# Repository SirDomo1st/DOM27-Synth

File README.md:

# D.O.M-27 Synth

My project is a fully DIY & anaglouge modular synth based on the eurorack system. It features 4 fundemental components of synthesis - a VCO, LFO, VCF & VCA. Because it is a modular synth & based on eurorack, this means that I can create more modules when I please to expand the functionality of my synth. There is no bottom case on the pannels as they are intended to me rack mounted on a system called eurorack. [Something like this](https://synthracks.com/shop/12u-studio-case?srsltid=AfmBOooeTvIxWJoqXPR5WksLaoWv1k82hauFViBRm4C1jTSQUN6ccUx9)

I made this my project is due to my passion for synth music and a want to learn to electronics. This was perfect as I could learn some basics of anaglouge electronics while also creating a useable, musical instrument. It was also perfect because modular synthesis is 
typically a very expensive hobby to get into.

### Total time spent on project: ~23 hours

## All 4 modules together 

## VCA pcb

## LFO pcb

## VCO pcb

## VCF pcb

## Project Schematics

Synth pannel CAD source files: https://www.mediafire.com/folder/19pjphztzjj5q/Synth+Pannel

A psu is included in my BOM because a eurorack system has specific power requiremnets. The psu sends +12v, -12v, 5v & GND to each individual module. It can also carry CV information. The psu also has a daisy chain ribbon as each module is powered individually. This is why they are fairly expensive, but also why one is required.

# D.O.M 27 Synth Bill of Materials
# Synthesizer Bill of Materials

| Value | Qty | Footprint | Source | Price | Where from |
|-------|-----|-----------|--------|-------|------------|
| 1.5k | 1 | Resistor_THT:R_Axial_DIN0207_L6.3mm_D2.5mm_P7.62mm_Horizontal | DS-20 VCF | 0.12 | Tayda |
| 100k | 44 | Resistor_THT:R_Axial_DIN0207_L6.3mm_D2.5mm_P7.62mm_Horizontal | DOMSynth, DS-20 VCF, Dom LFO, Dom VCA | 1.25 | Tayda |
| 100n | 4 | Capacitor_THT:C_Disc_D5.0mm_W2.5mm_P5.00mm | DS-20 VCF | 0.4 | Tayda |
| 10k | 27 | Resistor_THT:R_Axial_DIN0207_L6.3mm_D2.5mm_P7.62mm_Horizontal | DOMSynth, DS-20 VCF, Dom LFO, Dom VCA | 2.7 | Tayda |
| 10u | 4 | Capacitor_THT:C_Disc_D3.0mm_W1.6mm_P2.50mm | DS-20 VCF, Dom VCA | 0.15 | Tayda |
| 14k | 1 | Resistor_THT:R_Axial_DIN0207_L6.3mm_D2.5mm_P7.62mm_Horizontal | DOMSynth | ---- | |
| 150k | 2 | Resistor_THT:R_Axial_DIN0207_L6.3mm_D2.5mm_P7.62mm_Horizontal | Dom LFO | 0.25 | Tayda |
| 15k | 13 | Resistor_THT:R_Axial_DIN0207_L6.3mm_D2.5mm_P7.62mm_Horizontal | Dom VCA | 0.3 | Tayda |
| 1M | 3 | Resistor_THT:R_Axial_DIN0207_L6.3mm_D2.5mm_P7.62mm_Horizontal | DOMSynth | 0.15 | Tayda |
| 1N4148 | 5 | Diode_THT:D_DO-35_SOD27_P7.62mm_Horizontal | DOMSynth, Dom LFO | 0.05 | Tayda |
| 1k | 23 | Resistor_THT:R_Axial_DIN0207_L6.3mm_D2.5mm_P7.62mm_Horizontal | DOMSynth, DS-20 VCF, Dom LFO, Dom VCA | 0.45 | Tayda |
| 1k5 | 1 | Resistor_THT:R_Axial_DIN0207_L6.3mm_D2.5mm_P7.62mm_Horizontal | DOMSynth | 0.15 | Tayda |
| 1n | 2 | Capacitor_THT:C_Disc_D5.0mm_W2.5mm_P5.00mm | DS-20 VCF | 0.9 | Tayda |
| 1µF | 1 | Capacitor_THT:C_Disc_D5.0mm_W2.5mm_P5.00mm | DOMSynth | 0.12 | Tayda |
| 2.2k | 2 | Resistor_THT:R_Axial_DIN0207_L6.3mm_D2.5mm_P7.62mm_Horizontal | Dom LFO | 0.15 | Tayda |
| 2.2nF | 1 | Capacitor_THT:C_Disc_D5.0mm_W2.5mm_P5.00mm | DOMSynth | 0.06 | Tayda |
| 200k | 3 | Resistor_THT:R_Axial_DIN0207_L6.3mm_D2.5mm_P7.62mm_Horizontal | Dom VCA | 0.12 | Tayda |
| 220 | 4 | Resistor_THT:R_Axial_DIN0207_L6.3mm_D2.5mm_P7.62mm_Horizontal | DS-20 VCF | 0.8 | Tayda |
| 220k | 1 | Resistor_THT:R_Axial_DIN0207_L6.3mm_D2.5mm_P7.62mm_Horizontal | DS-20 VCF | 0.15 | Tayda |
| 250k | 1 | Potentiometer_THT:Potentiometer_Alpha_RD901F-40-00D_Single_Vertical | DOMSynth | 1.29 | Tayda |
| 33k | 4 | Resistor_THT:R_Axial_DIN0207_L6.3mm_D2.5mm_P7.62mm_Horizontal | DOMSynth, Dom VCA | 0.15 | Tayda |
| 4.7k | 5 | Resistor_THT:R_Axial_DIN0207_L6.3mm_D2.5mm_P7.62mm_Horizontal | DS-20 VCF, Dom LFO | 0.15 | Tayda |
| 4.7n | 1 | Capacitor_THT:C_Disc_D5.0mm_W2.5mm_P5.00mm | DS-20 VCF | 0.07 | Tayda |
| 470k | 1 | Resistor_THT:R_Axial_DIN0207_L6.3mm_D2.5mm_P7.62mm_Horizontal | DS-20 VCF | 0.15 | Tayda |
| 470n | 1 | Capacitor_THT:C_Disc_D5.0mm_W2.5mm_P5.00mm | DS-20 VCF | 0.08 | Tayda |
| 47k | 1 | Resistor_THT:R_Axial_DIN0207_L6.3mm_D2.5mm_P7.62mm_Horizontal | DS-20 VCF | 0.15 | Tayda |
| 47n | 2 | Capacitor_THT:C_Disc_D5.0mm_W2.5mm_P5.00mm | Dom LFO | 0.13 | Tayda |
| 500k | 2 | Potentiometer_THT:Potentiometer_Alpha_RD901F-40-00D_Single_Vertical | Dom LFO | 1.34 | Tayda |
| 5k | 3 | Potentiometer_THT:Potentiometer_Bourns_3296P_Horizontal | Dom VCA | 0.18 | Tayda |
| 68k | 2 | Resistor_THT:R_Axial_DIN0207_L6.3mm_D2.5mm_P7.62mm_Horizontal | DOMSynth | 0.15 | Tayda |
| 74HC14 | 1 | Package_DIP:DIP-14_W7.62mm | DOMSynth | 0.66 | Tayda |
| Audio Jack | 23 | Connector_Audio:Jack_3.5mm_QingPu_WQP-PJ398SM_Vertical_CircularHoles | DOMSynth, DS-20 VCF, Dom LFO, Dom VCA | 8.97 | Tayda |
| BC548 | 10 | Package_TO_SOT_THT:TO-92_Inline | DOMSynth, Dom VCA | 0.4 | Tayda |
| BC557 | 2 | Package_TO_SOT_THT:TO-92_Inline | DS-20 VCF | 0.06 | Tayda |
| BC558 | 1 | Package_TO_SOT_THT:TO-92_Inline | DOMSynth | 0.04 | Tayda |
| 10u Polarised | 2 | Capacitor_THT:CP_Radial_D5.0mm_P2.50mm | Dom VCA | 0.06 | Tayda |
| Conn_02x08_Odd_Even | 2 | Connector_IDC:IDC-Header_2x08_P2.54mm_Vertical | DS-20 VCF, Dom VCA | --- | |
| Conn_02x08_Top_Bottom | 2 | Connector_IDC:IDC-Header_2x08_P2.54mm_Vertical | DOMSynth, Dom LFO | --- | |
| LED | 2 | LED_THT:LED_D5.0mm | DS-20 VCF | 0.048 | Tayda |
| LM13700 | 2 | Package_TO_SOT_SMD:SOT-23-5 | DS-20 VCF | 4.7 | Tayda |
| TL072 | 10 | Package_DIP:DIP-8_W7.62mm | DS-20 VCF, Dom VCA | 14.9 | Tayda |
| TL074 | 8 | Package_DIP:DIP-14_W7.62mm | DOMSynth, Dom LFO | 4.72 | Tayda |
| 100k | 13 | Pot | | 8.71 | Tayda |
| 10k | 1 | Pot | | 0.67 | Tayda |
| 1M | 1 | Pot | | 0.67 | Tayda |
| 1k | 2 | MusicThingModular:BOURNS_3362P_TRIMMER | | 0.12 | Tayda |
| 10k | 3 | Potentiometer_THT:Potentiometer_Bourns_3296P_Horizontal | | 0.18 | Tayda |
| | | | | | Tayda |
| Power Male | 4 | | | 1.2 | |
| Power Female | 4 | | | 0.52 | |
| Tayda Shipping | 1 | | | 9.25 | Tayda |
| | | | | | |
| PSU | 1 | Behringer System 55 CP1A Power Supply Module | | 62.56 | Gear4Music |
| G4M Shipping | | | | 2.71 | |
| | | | | | |
| PCB 110x60 | 2 | | | 13 | JLB PCB |
| PCB 110x40 | 2 | | | 11.4 | JLB PCB |
| JLB Shipping | 1 | | | 3.12 | |
| | | | | | |
| **Total Price** | | | | **$160.77** |

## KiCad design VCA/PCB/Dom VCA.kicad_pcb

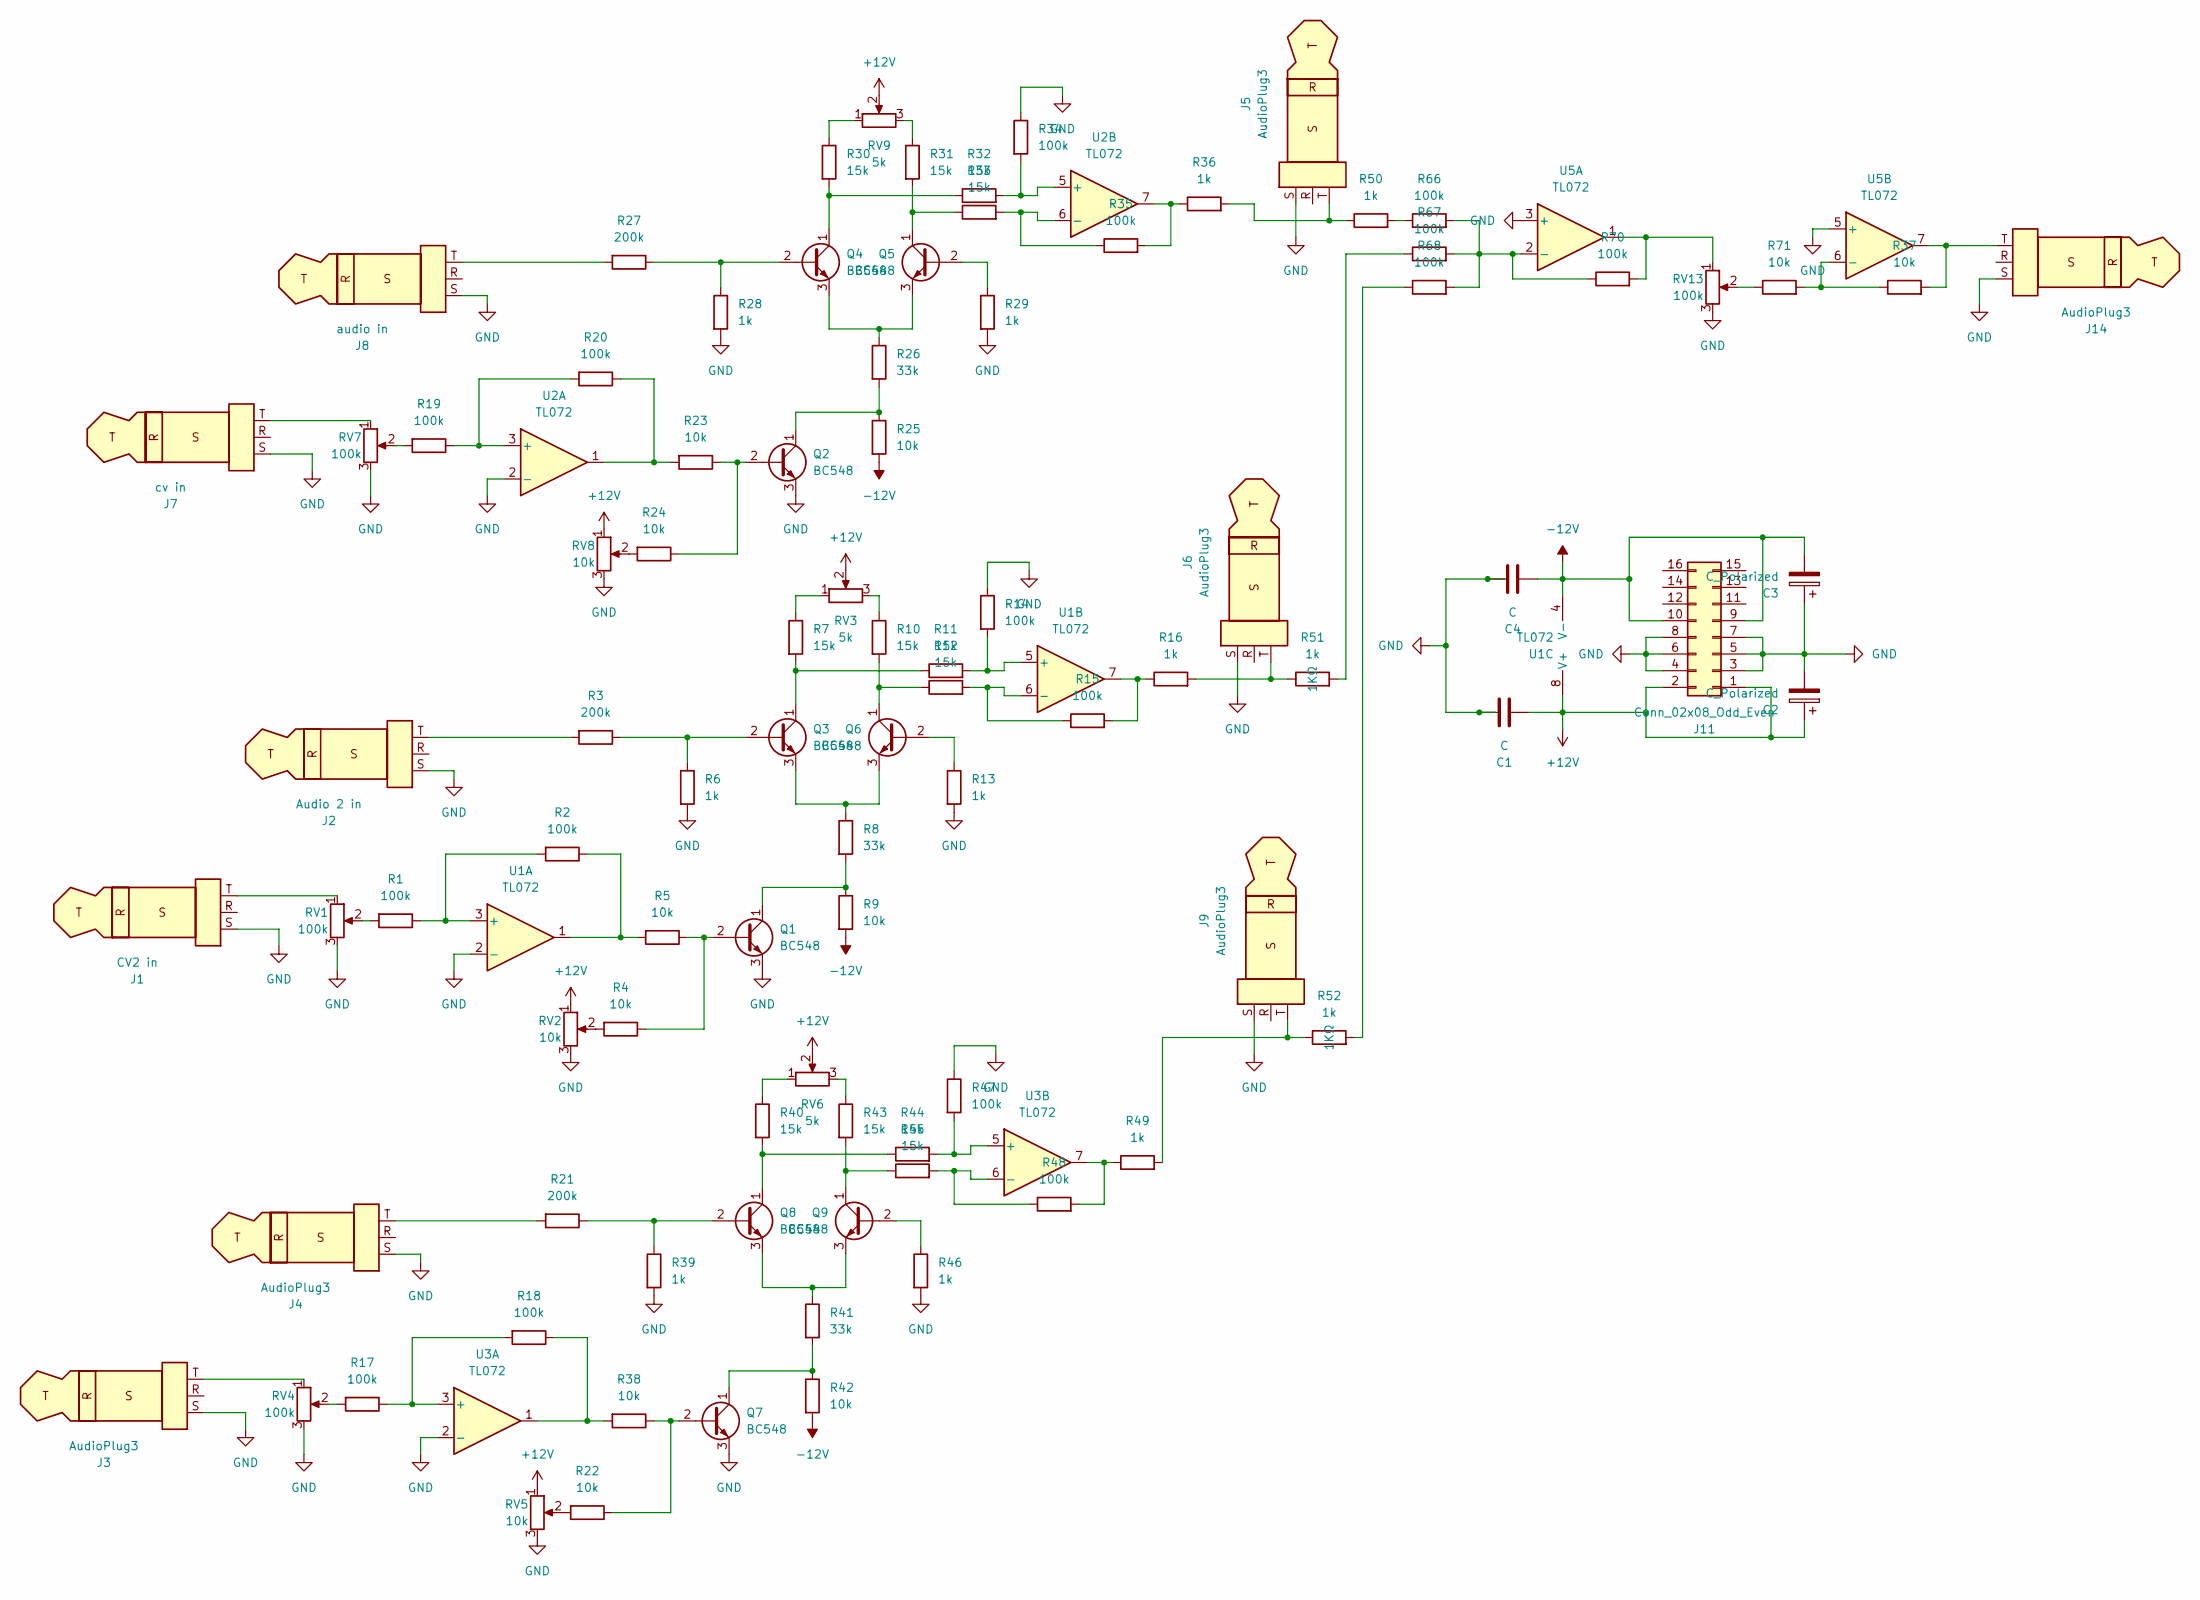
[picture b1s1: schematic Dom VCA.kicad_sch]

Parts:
C1, C4: C; C_Disc_D3.0mm_W1.6mm_P2.50mm
C2, C3: C_Polarized; CP_Radial_D5.0mm_P2.50mm
J1: CV2 in; Jack_3.5mm_QingPu_WQP-PJ398SM_Vertical_CircularHoles
J2: Audio 2 in; Jack_3.5mm_QingPu_WQP-PJ398SM_Vertical_CircularHoles
J3, J4, J5, J6, J9, J14: AudioPlug3; Jack_3.5mm_QingPu_WQP-PJ398SM_Vertical_CircularHoles
J7: cv in; Jack_3.5mm_QingPu_WQP-PJ398SM_Vertical_CircularHoles
J8: audio in; Jack_3.5mm_QingPu_WQP-PJ398SM_Vertical_CircularHoles
J11: Conn_02x08_Odd_Even; IDC-Header_2x08_P2.54mm_Vertical
Q1, Q2, Q3, Q4, Q5, Q6, Q7, Q8, Q9: BC548; TO-92_Inline
R1, R2, R14, R15, R17, R18, R19, R20, R34, R35, R47, R48, R66, R67, R68, R70: 100k; R_Axial_DIN0207_L6.3mm_D2.5mm_P7.62mm_Horizontal
R3, R21, R27: 200k; R_Axial_DIN0207_L6.3mm_D2.5mm_P7.62mm_Horizontal
R4, R5, R9, R22, R23, R24, R25, R37, R38, R42, R71: 10k; R_Axial_DIN0207_L6.3mm_D2.5mm_P7.62mm_Horizontal
R6, R13, R16, R28, R29, R36, R39, R46, R49, R50, R51, R52: 1k; R_Axial_DIN0207_L6.3mm_D2.5mm_P7.62mm_Horizontal
R7, R10, R11, R12, R30, R31, R32, R33, R40, R43, R44, R45: 15k; R_Axial_DIN0207_L6.3mm_D2.5mm_P7.62mm_Horizontal
R8, R26, R41: 33k; R_Axial_DIN0207_L6.3mm_D2.5mm_P7.62mm_Horizontal
RV1, RV4, RV7, RV13: 100k; Potentiometer_Alpha_RD901F-40-00D_Single_Vertical
RV2, RV5, RV8: 10k; Potentiometer_Bourns_3296P_Horizontal
RV3, RV6, RV9: 5k; Potentiometer_Bourns_3296P_Horizontal
U1, U2, U3, U5: TL072; DIP-8_W7.62mm

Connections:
+12V: C1.1, C2.1, J11.1, J11.2, RV2.1, RV3.2, RV5.1, RV6.2, RV8.1, RV9.2, U1.8 (V+)
-12V: C3.2, C4.1, J11.9, J11.10, R9.2, R25.2, R42.2, U1.4 (V-)
GND: C1.2, C2.2, C3.1, C4.2, J1.S, J2.S, J3.S, J4.S, J5.S, J6.S, J7.S, J8.S, J9.S, J11.3, J11.4, J11.5, J11.6, J11.7, J11.8, J14.S, Q1.3 (E), Q2.3 (E), Q7.3 (E), R6.2, R13.2, R14.1, R28.2, R29.2, R34.1, R39.2, R46.2, R47.1, RV1.3, RV2.3, RV4.3, RV5.3, RV7.3, RV8.3, RV13.3, U1.2 (-), U2.2 (-), U3.2 (-), U5.3 (+), U5.5 (+)
unnamed: J1.T, RV1.1
unnamed: J2.T, R3.2
unnamed: J3.T, RV4.1
unnamed: J4.T, R21.2
unnamed: J5.T, R36.2, R50.1
unnamed: J6.T, R16.2, R51.1
unnamed: J7.T, RV7.1
unnamed: J8.T, R27.2
unnamed: J9.T, R49.2, R52.1
unnamed: J14.T, R37.2, U5.7
unnamed: Q1.2 (B), R4.1, R5.1
unnamed: Q1.1 (C), R8.2, R9.1
unnamed: Q2.2 (B), R23.1, R24.1
unnamed: Q2.1 (C), R25.1, R26.2
unnamed: Q3.2 (B), R3.1, R6.1
unnamed: Q3.1 (C), R7.2, R11.1
unnamed: Q3.3 (E), Q6.3 (E), R8.1
unnamed: Q4.2 (B), R27.1, R28.1
unnamed: Q4.1 (C), R30.2, R32.1
unnamed: Q4.3 (E), Q5.3 (E), R26.1
unnamed: Q5.2 (B), R29.1
unnamed: Q5.1 (C), R31.2, R33.1
unnamed: Q6.2 (B), R13.1
unnamed: Q6.1 (C), R10.2, R12.1
unnamed: Q7.2 (B), R22.1, R38.1
unnamed: Q7.1 (C), R41.2, R42.1
unnamed: Q8.2 (B), R21.1, R39.1
unnamed: Q8.1 (C), R40.2, R44.1
unnamed: Q8.3 (E), Q9.3 (E), R41.1
unnamed: Q9.2 (B), R46.1
unnamed: Q9.1 (C), R43.2, R45.1
unnamed: R1.2, RV1.2
unnamed: R2.1, R5.2, U1.1
unnamed: R4.2, RV2.2
unnamed: R7.1, RV3.1
unnamed: R10.1, RV3.3
unnamed: R15.2, R16.1, U1.7
unnamed: R17.2, RV4.2
unnamed: R18.1, R38.2, U3.1
unnamed: R19.2, RV7.2
unnamed: R20.1, R23.2, U2.1
unnamed: R22.2, RV5.2
unnamed: R24.2, RV8.2
unnamed: R30.1, RV9.1
unnamed: R31.1, RV9.3
unnamed: R35.2, R36.1, U2.7
unnamed: R40.1, RV6.1
unnamed: R43.1, RV6.3
unnamed: R48.2, R49.1, U3.7
unnamed: R50.2, R66.1
unnamed: R51.2, R67.1
unnamed: R52.2, R68.1
unnamed: R70.2, RV13.1, U5.1
unnamed: R71.1, RV13.2
unnamed: R1.1, R2.2, U1.3 (+)
unnamed: R11.2, R14.2, U1.5 (+)
unnamed: R12.2, R15.1, U1.6 (-)
unnamed: R19.1, R20.2, U2.3 (+)
unnamed: R32.2, R34.2, U2.5 (+)
unnamed: R33.2, R35.1, U2.6 (-)
unnamed: R17.1, R18.2, U3.3 (+)
unnamed: R44.2, R47.2, U3.5 (+)
unnamed: R45.2, R48.1, U3.6 (-)
unnamed: R66.2, R67.2, R68.2, R70.1, U5.2 (-)
unnamed: R37.1, R71.2, U5.6 (-)

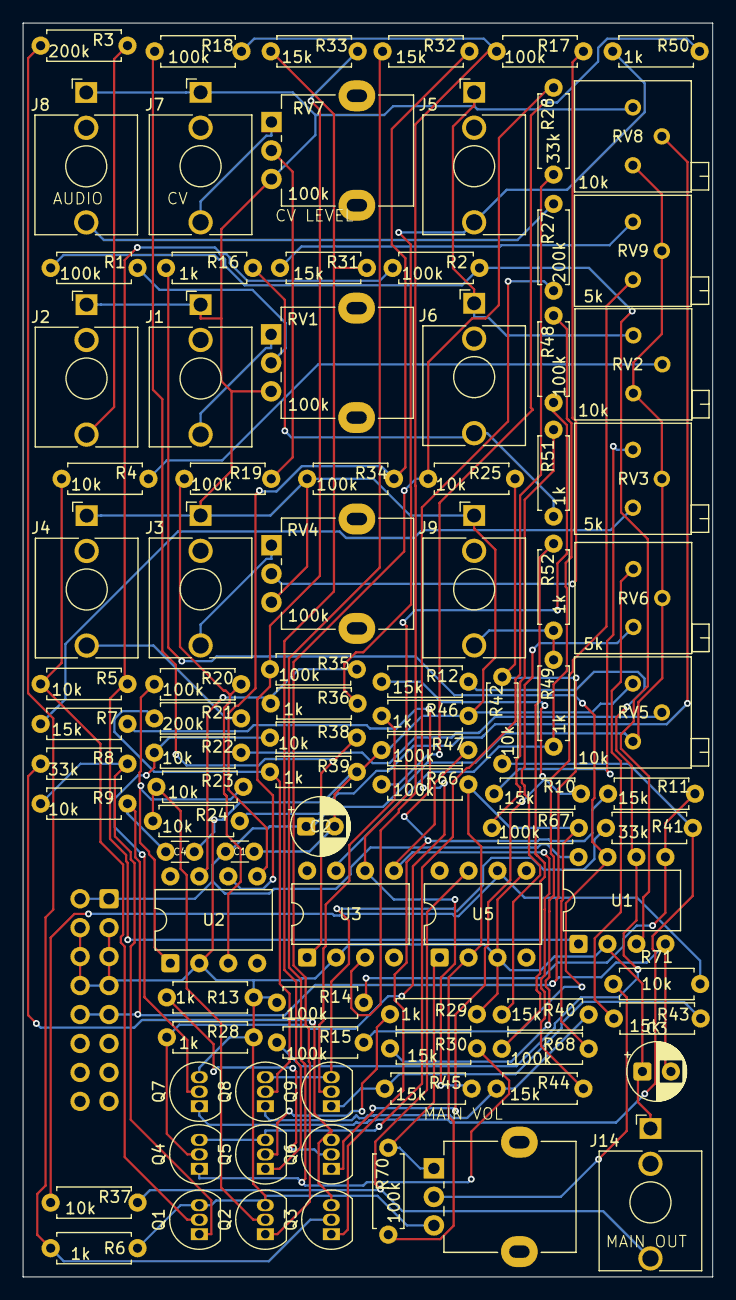
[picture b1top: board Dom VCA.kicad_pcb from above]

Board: 2 copper layers, 60.5 x 110.0 mm, 95 parts (1 on the bottom side), 68 nets.

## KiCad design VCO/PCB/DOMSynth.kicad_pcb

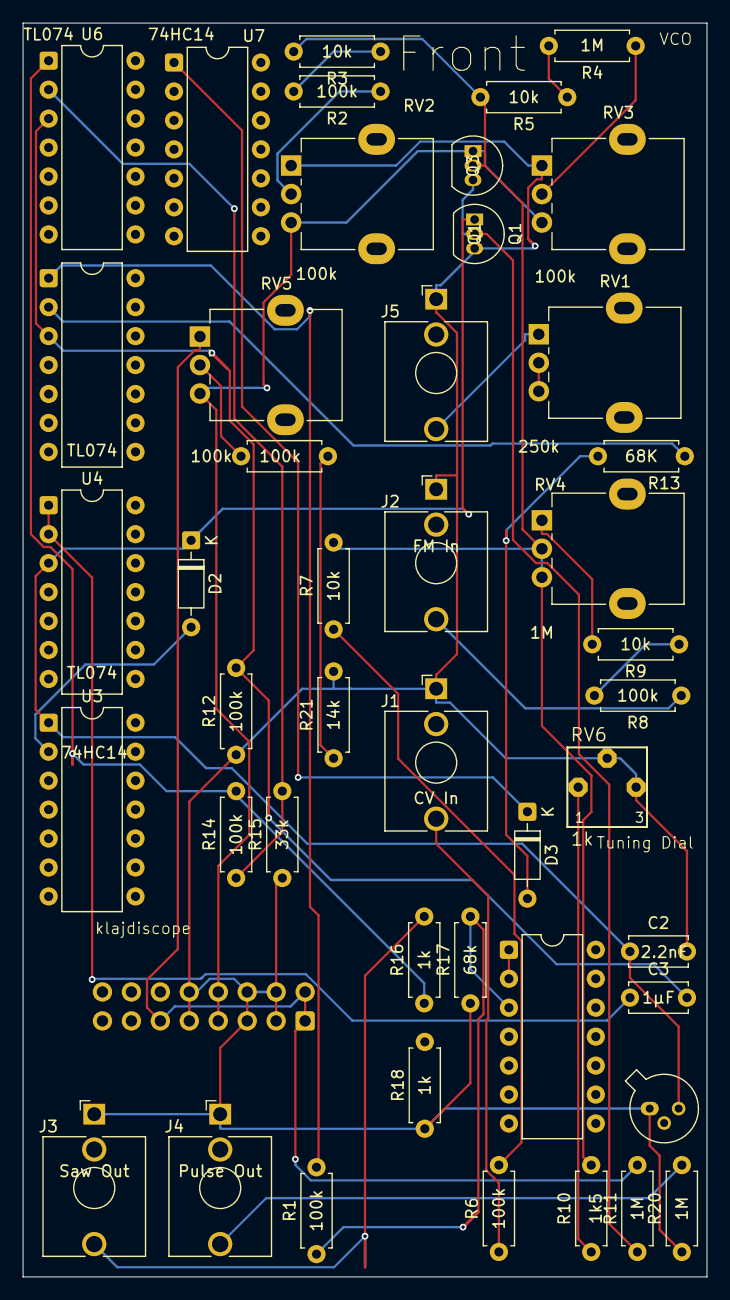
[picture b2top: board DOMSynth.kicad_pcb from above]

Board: 2 copper layers, 60.0 x 110.0 mm, 46 parts (1 on the bottom side), 33 nets.

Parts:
C2: 2.2nF; C_Disc_D5.0mm_W2.5mm_P5.00mm
C3: 1µF; C_Disc_D5.0mm_W2.5mm_P5.00mm
D2, D3: 1N4148; D_DO-35_SOD27_P7.62mm_Horizontal
J1: CV In; Jack_3.5mm_QingPu_WQP-PJ398SM_Vertical_CircularHoles
J2: FM In; Jack_3.5mm_QingPu_WQP-PJ398SM_Vertical_CircularHoles
J3: Saw Out; Jack_3.5mm_QingPu_WQP-PJ398SM_Vertical_CircularHoles
J4: Pulse Out; Jack_3.5mm_QingPu_WQP-PJ398SM_Vertical_CircularHoles
J5: PMW In; Jack_3.5mm_QingPu_WQP-PJ398SM_Vertical_CircularHoles
J6: Conn_02x08_Top_Bottom; IDC-Header_2x08_P2.54mm_Vertical
Q1: BC548; TO-92_Inline
Q3: BC558; TO-92_Inline
Q5: BC107; TO-18-3
R1, R2, R6, R8, R12, R14, R22: 100k; R_Axial_DIN0207_L6.3mm_D2.5mm_P7.62mm_Horizontal
R3, R5, R7, R9: 10k; R_Axial_DIN0207_L6.3mm_D2.5mm_P7.62mm_Horizontal
R4, R11, R20: 1M; R_Axial_DIN0207_L6.3mm_D2.5mm_P7.62mm_Horizontal
R10: 1k5; R_Axial_DIN0207_L6.3mm_D2.5mm_P7.62mm_Horizontal
R13: 68K; R_Axial_DIN0207_L6.3mm_D2.5mm_P7.62mm_Horizontal
R15: 33k; R_Axial_DIN0207_L6.3mm_D2.5mm_P7.62mm_Horizontal
R16, R18: 1k; R_Axial_DIN0207_L6.3mm_D2.5mm_P7.62mm_Horizontal
R17: 68k; R_Axial_DIN0207_L6.3mm_D2.5mm_P7.62mm_Horizontal
R21: 14k; R_Axial_DIN0207_L6.3mm_D2.5mm_P7.62mm_Horizontal
RV1: 250k; Potentiometer_Alpha_RD901F-40-00D_Single_Vertical
RV2, RV3, RV5: 100k; Potentiometer_Alpha_RD901F-40-00D_Single_Vertical
RV4: 1M; Potentiometer_Alpha_RD901F-40-00D_Single_Vertical
RV6: 1k; BOURNS_3362P_TRIMMER
U1, U4, U5, U6: TL074; DIP-14_W7.62mm
U3, U7: 74HC14; DIP-14_W7.62mm

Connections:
+12V: J6.1, J6.2, J6.11, R11.2, RV5.1
-12V: J6.7, J6.8, Q3.1 (C), RV2.3, RV3.3, RV5.3
GND: C2.2, J1.S, J2.S, J3.S, J4.S, J5.S, J6.3, J6.4, J6.5, J6.6, J6.9, J6.10, Q1.3 (E), Q5.1 (E), R12.1, R15.1, R17.1, R18.1, R20.1, R21.2, RV2.1, RV3.1, RV6.2, RV6.3
unnamed: D2.2 (A), U3.2
unnamed: C2.1, D2.1 (K), Q1.1 (C), Q5.3 (C), U3.1, U4.3 (+)
unnamed: D3.2 (A), R13.2
unnamed: D3.1 (K), U7.1
unnamed: J1.T, R6.1
unnamed: J2.T, R8.1
unnamed: J3.T, R16.2
unnamed: J4.T, R20.2
unnamed: J5.T, RV1.1
unnamed: Q1.2 (B), Q3.3 (E), R11.1
unnamed: Q3.2 (B), R3.2, R5.2, R7.2, R10.2, RV4.2, RV4.3
unnamed: R1.2, U5.1
unnamed: R2.1, RV2.2
unnamed: R2.2, R3.1
unnamed: R4.1, RV3.2
unnamed: R4.2, R5.1
unnamed: R6.2, R7.1
unnamed: R8.2, R9.1
unnamed: R9.2, RV4.1
unnamed: R10.1, RV6.1
unnamed: RV1.2, RV1.3
unnamed: R14.2, R16.1, U6.1
unnamed: R21.1, R22.2
unnamed: R22.1, RV5.2
unnamed: R1.1, R17.2, U1.3 (+)
unnamed: U1.1, U1.2 (-)
unnamed: C3.1, U4.1, U4.2 (-)
unnamed: C3.2, R12.2, U5.3 (+), U6.3 (+)
unnamed: R13.1, U5.2 (-)
unnamed: R14.1, R15.2, U6.2 (-)

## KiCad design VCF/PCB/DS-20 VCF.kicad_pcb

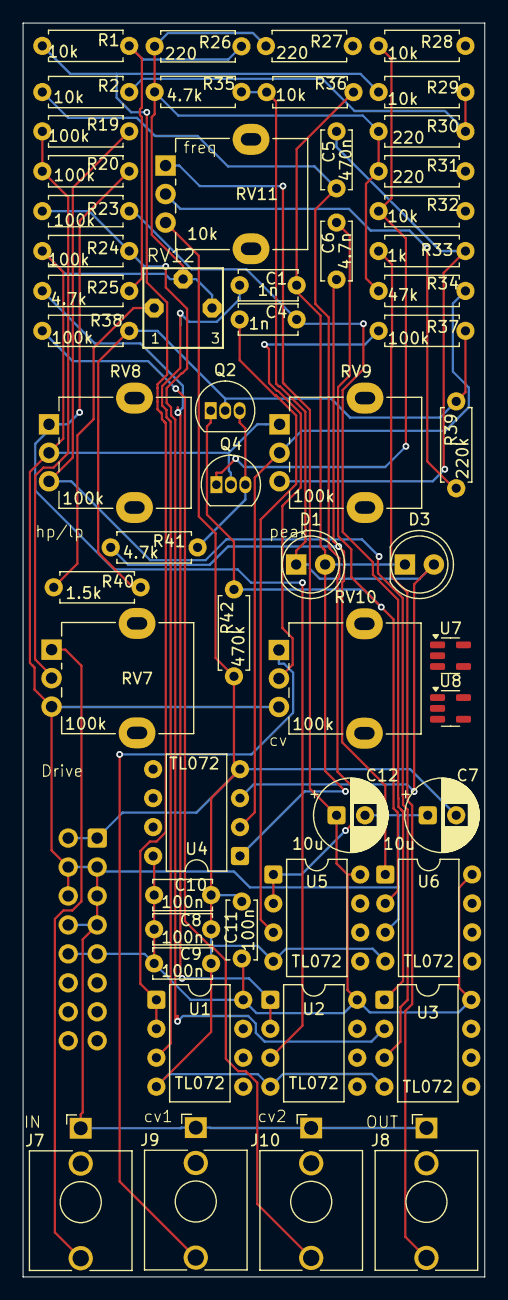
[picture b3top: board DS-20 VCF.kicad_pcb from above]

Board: 2 copper layers, 40.5 x 110.0 mm, 57 parts (1 on the bottom side), 31 nets.

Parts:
C1, C4: 1n; C_Disc_D5.0mm_W2.5mm_P5.00mm
C5: 470n; C_Disc_D5.0mm_W2.5mm_P5.00mm
C6: 4.7n; C_Disc_D5.0mm_W2.5mm_P5.00mm
C7, C12: 10u; CP_Radial_D6.3mm_P2.50mm
C8, C9, C10, C11: 100n; C_Disc_D5.0mm_W2.5mm_P5.00mm
D1, D3: LED; LED_D5.0mm
J7, J8, J9, J10: AudioPlug3; Jack_3.5mm_QingPu_WQP-PJ398SM_Vertical_CircularHoles
J12: Conn_02x08_Odd_Even; IDC-Header_2x08_P2.54mm_Vertical
Q2, Q4: BC557; TO-92_Inline
R1, R2, R28, R29, R32, R36: 10k; R_Axial_DIN0207_L6.3mm_D2.5mm_P7.62mm_Horizontal
R19, R20, R23, R24, R37, R38: 100k; R_Axial_DIN0207_L6.3mm_D2.5mm_P7.62mm_Horizontal
R25, R35, R41: 4.7k; R_Axial_DIN0207_L6.3mm_D2.5mm_P7.62mm_Horizontal
R26, R27, R30, R31: 220; R_Axial_DIN0207_L6.3mm_D2.5mm_P7.62mm_Horizontal
R33: 1k; R_Axial_DIN0207_L6.3mm_D2.5mm_P7.62mm_Horizontal
R34: 47k; R_Axial_DIN0207_L6.3mm_D2.5mm_P7.62mm_Horizontal
R39: 220k; R_Axial_DIN0207_L6.3mm_D2.5mm_P7.62mm_Horizontal
R40: 1.5k; R_Axial_DIN0207_L6.3mm_D2.5mm_P7.62mm_Horizontal
R42: 470k; R_Axial_DIN0207_L6.3mm_D2.5mm_P7.62mm_Horizontal
RV7, RV8, RV9, RV10: 100k; Potentiometer_Alpha_RD901F-40-00D_Single_Vertical
RV11: 10k; Potentiometer_Alpha_RD901F-40-00D_Single_Vertical
RV12: 1k; BOURNS_3362P_TRIMMER
U1, U2, U3, U4, U5, U6: TL072; DIP-8_W7.62mm
U7, U8: LM13700; SOT-23-5

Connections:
+12V: C8.1, C9.1, C10.1, C11.1, C12.1, J12.9, J12.10, RV11.1, U1.8 (V+), U2.8 (V+), U3.8 (V+), U4.8 (V+), U5.8 (V+), U6.8 (V+)
-12V: C7.2, C8.2, C9.2, C10.2, C11.2, J12.1, J12.2, R42.1, RV11.3, U1.4 (V-), U2.4 (V-), U3.4 (V-), U4.4 (V-), U5.4 (V-), U6.4 (V-)
GND: C7.1, C12.2, J7.S, J8.S, J9.S, J10.S, J12.3, J12.4, J12.5, J12.6, J12.7, J12.8, Q4.2 (B), R24.1, R26.1, R27.1, R30.1, R31.1, R34.1, R35.1, RV7.3, RV8.2, RV9.1, RV10.3, RV12.2, RV12.3, U6.3 (+)
unnamed: C4.2, R23.2, U3.1
unnamed: C5.2, R33.2, RV9.3
unnamed: C6.1, R41.1, U6.1
unnamed: C1.2, D1.2 (A), D3.1 (K), R36.2, U4.1
unnamed: D1.1 (K), D3.2 (A), R35.2, R36.1, U4.3 (+)
unnamed: J7.T, RV7.1
unnamed: J8.T, R33.1
unnamed: J9.T, RV10.1
unnamed: J10.T, R38.1
unnamed: Q2.2 (B), R37.2, R38.2, R39.2, R40.2
unnamed: C6.2, Q2.1 (C), R42.2, U6.2 (-)
unnamed: Q2.3 (E), Q4.3 (E), R41.2
unnamed: Q4.1 (C), R28.1, R32.1
unnamed: R19.1, R20.1, RV7.2
unnamed: R37.1, RV10.2
unnamed: R39.1, RV11.2
unnamed: R40.1, RV12.1
unnamed: C1.1, U1.3 (+)
unnamed: R1.1, R29.1, U1.1, U1.2 (-)
unnamed: R20.2, RV8.1, U2.3 (+)
unnamed: R25.1, U2.1, U2.2 (-)
unnamed: R19.2, RV8.3, U3.3 (+)
unnamed: R23.1, R24.2, U3.2 (-)
unnamed: R34.2, RV9.2, U4.2 (-)
unnamed: C4.1, U5.3 (+)
unnamed: C5.1, R2.1, U5.1, U5.2 (-)
unnamed: R2.2, R29.2, R30.2
unnamed: R1.2, R25.2, R26.2

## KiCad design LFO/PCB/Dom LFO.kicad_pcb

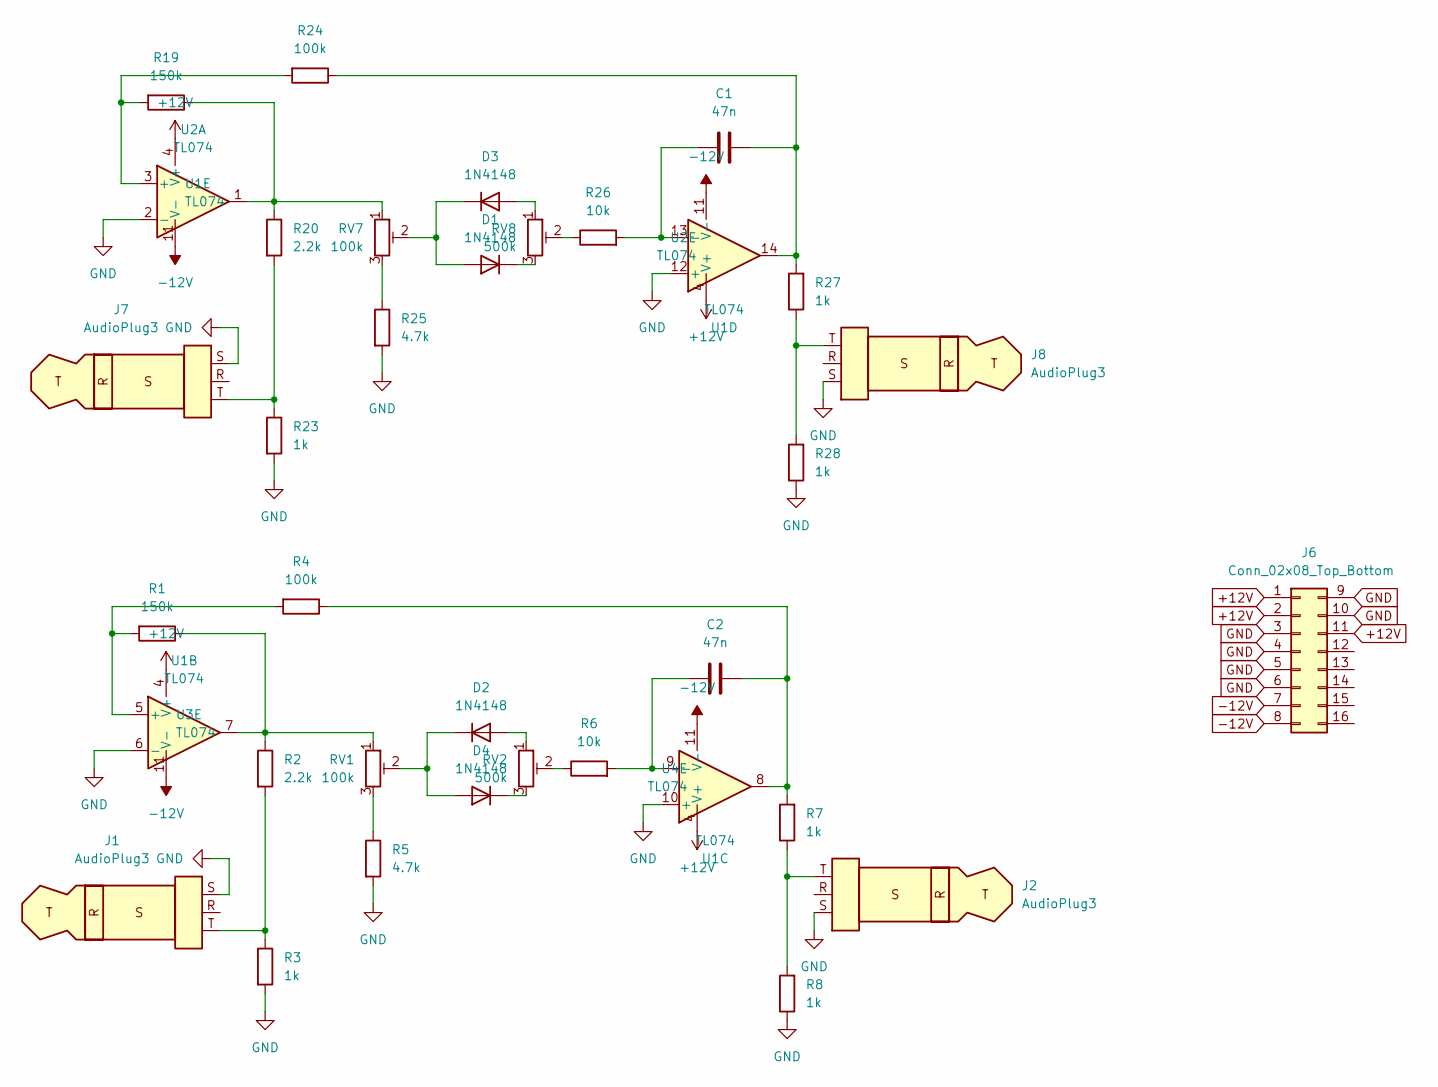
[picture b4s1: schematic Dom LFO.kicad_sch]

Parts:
C1, C2: 47n; C_Disc_D5.0mm_W2.5mm_P5.00mm
D1, D2, D3, D4: 1N4148; D_DO-35_SOD27_P7.62mm_Horizontal
J1, J2, J7, J8: AudioPlug3; Jack_3.5mm_QingPu_WQP-PJ398SM_Vertical_CircularHoles
J6: Conn_02x08_Top_Bottom; IDC-Header_2x08_P2.54mm_Vertical
R1, R19: 150k; R_Axial_DIN0207_L6.3mm_D2.5mm_P7.62mm_Horizontal
R2, R20: 2.2k; R_Axial_DIN0207_L6.3mm_D2.5mm_P7.62mm_Horizontal
R3, R7, R8, R23, R27, R28: 1k; R_Axial_DIN0207_L6.3mm_D2.5mm_P7.62mm_Horizontal
R4, R24: 100k; R_Axial_DIN0207_L6.3mm_D2.5mm_P7.62mm_Horizontal
R5, R25: 4.7k; R_Axial_DIN0207_L6.3mm_D2.5mm_P7.62mm_Horizontal
R6, R26: 10k; R_Axial_DIN0207_L6.3mm_D2.5mm_P7.62mm_Horizontal
RV1, RV7: 100k; Potentiometer_Alpha_RD901F-40-00D_Single_Vertical
RV2, RV8: 500k; Potentiometer_Alpha_RD901F-40-00D_Single_Vertical
U1, U2, U3, U4: TL074; DIP-14_W7.62mm

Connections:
+12V: J6.1, J6.2, J6.11, U1.4 (V+), U2.4 (V+), U3.4 (V+), U4.4 (V+)
-12V: J6.7, J6.8, U1.11 (V-), U2.11 (V-), U3.11 (V-), U4.11 (V-)
GND: J1.S, J2.S, J6.3, J6.4, J6.5, J6.6, J6.9, J6.10, J7.S, J8.S, R3.2, R5.2, R8.1, R23.2, R25.2, R28.1, U1.6 (-), U1.10 (+), U1.12 (+), U2.2 (-)
unnamed: C1.2, R24.1, R27.2, U1.14
unnamed: C2.2, R4.1, R7.2, U1.8
unnamed: D1.2 (A), D3.1 (K), RV7.2
unnamed: D1.1 (K), RV8.3
unnamed: D2.2 (A), RV2.1
unnamed: D2.1 (K), D4.2 (A), RV1.2
unnamed: D3.2 (A), RV8.1
unnamed: D4.1 (K), RV2.3
unnamed: J1.T, R2.2, R3.1
unnamed: J2.T, R7.1, R8.2
unnamed: J7.T, R20.2, R23.1
unnamed: J8.T, R27.1, R28.2
unnamed: R1.1, R2.1, RV1.1, U1.7
unnamed: R5.1, RV1.3
unnamed: R6.1, RV2.2
unnamed: R19.1, R20.1, RV7.1, U2.1
unnamed: R25.1, RV7.3
unnamed: R26.1, RV8.2
unnamed: R1.2, R4.2, U1.5 (+)
unnamed: C2.1, R6.2, U1.9 (-)
unnamed: C1.1, R26.2, U1.13 (-)
unnamed: R19.2, R24.2, U2.3 (+)

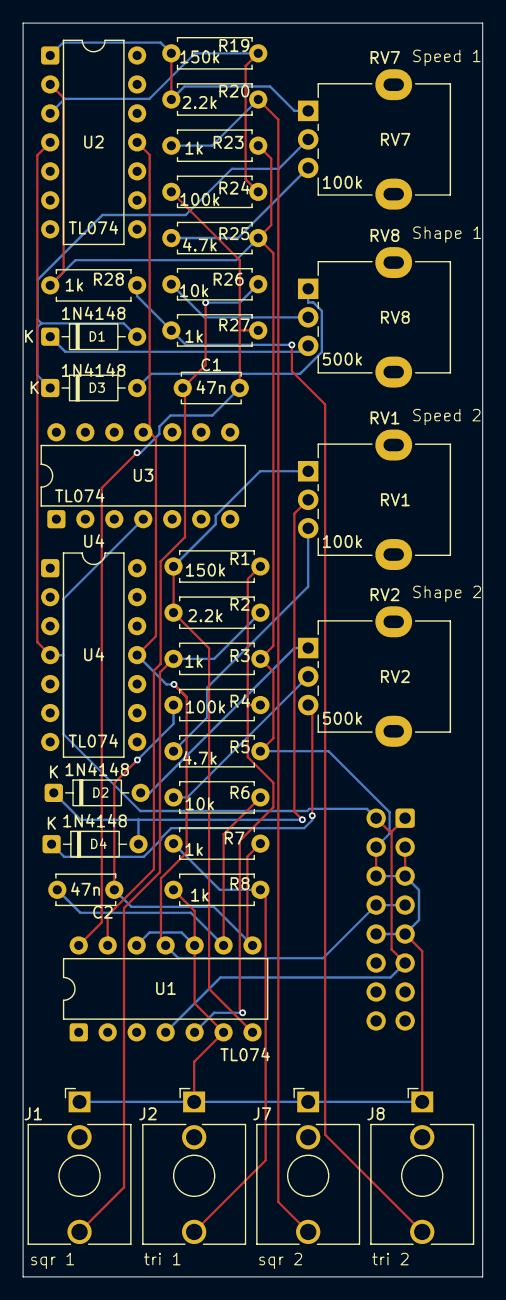
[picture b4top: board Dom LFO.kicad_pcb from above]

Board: 2 copper layers, 40.3 x 109.9 mm, 35 parts (1 on the bottom side), 25 nets.

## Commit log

2025-07-07 file added
